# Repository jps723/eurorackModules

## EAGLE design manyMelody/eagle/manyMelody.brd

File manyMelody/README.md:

# manyMelody Synth

# **This is currently incomplete and I'll be updating shortly.** 

## To do: 
1) Write code for CV Input. 
2) Clean up synth defs
3) Adjust min/max on all parameters. 

This is a eurorack version of the [Feather Synth](https://github.com/jps723/featherSynth/), moving over to a Teensy 3.6. 

**Design Notes:**

The base software for this module uses these inputs to control an auto-advancing sequence of notes.  The knobs control the root note, the scale, the probability that the note will play, and the tempo.  Pressing the button cycles through different waveforms/oscillator types.

**Synthesizer Design**
The synth is a dual-oscillator synthesizer, each with independent bi-quad filters and envelopes.  The envelope settings are static while the filters are set to Low Pass Filters with the frequency cutoff randomly changing between two static values based on probability (math within the software -- this is unrelated to the probability knob).   

**Controls**
Root Note (Tonic)
The note from which the scale begins.  By default the notes to choose from range from A0 to C8

**Scale Selector**
There are a total of seven scales to choose from, beginning with the major scale, and then each mode variant resulting in the 7 diatonic modes in western music.

**Probability**
The probability that the note will be played, as calculated by comparing the knob’s position to a randomly generated number. Ex. 0-100% chance of playing

**Tempo**
The overall tempo of the sequence as determined by delay between each note

**Waveform Selector**
This is a series of oscillator combinations that get cycled through using the button.

## **Code**
The code is broken up into two separate files:  

**featherSynth.ino**
This is our primary code and is broken up into two sections: setup and loop.  Setup runs once, while loop cycles through continuously after the setup code has been executed. All of the code above the setup() function is required to call the library we are using (Audio.h), call our reference file (scales.h), and initialize our global variables. All of the code below the main loop() are functions that are called from either within setup() or loop().

Setup() contains code for setting audio memory allocation, pin assignment, and a function called oscillatorSetup() that is used for setting initial values of our oscillators/envelopes, etc.  These will mostly get overwritten by the loop however we want to define our instrument before the program begins to cycle.  

loop() contains the bulk of our code. We have a function called buttonHandler() that is used for managing what we want to happen when we press the button. If you find this function below, you can add further oscillator combinations.  Our potentiometer readings are assigned to the Feather pins here as well. If you want to change the order of the knobs, do it here.

The nested for() loop is used to populate the rootScaled array.  This determines what notes are in the sequence and the order that they’re arranged in.  There are two arrangements to choose from, either climbing the scale, or random selection.  Only one can be used at a time.

The frequency is calculated using a formula that stems from midi note values which are a standard form of notation for relating to frequency.

The frequency cutoff is currently assigned a 50% chance of being 7000 hz, or 2000 hz. Experiment with these numbers.

The probabilityOfPlaying variable is compared to a random value between 0 and 100.  Since probabilityOfPlaying is also a value between 0 and 100, this is treated as a percentage.  You can experiment with these values.

playOsc1() and playOsc2() functions take one argument (frequency) which is calculated via the explanation above.  These functions also contain the methods for dictating the ADSR envelope values which are hardcoded and can be adjusted and should be experimented with. The filter frequency cutoff and delayTime are also embedded in these functions, with delayTime being used to set the time between notes (our tempo).

The buttonHandler function counts the button presses and uses that count to cycle through the 7 different oscillator combinations in the switch statement.

**scales.h**
scales.h is a reference file where we have all of our different scales stored.  The base code has 7 scales (each of the diatonic modes) spread out across two octaves, with the root note at each octave playing at a 3:1 ratio to everything else.  This results in an 18 note array (an array with 18 indices), which are all a part of another array that contains each of these arrays (a total of 7).  If you were to add an 8th scale with 18 notes, then the scales[][] array should be initialized as scales[8][18].  This would also need to be changed in the .ino sketch in the rootScaled[][] array.  

Currently, if the knob is turned all the way to the left, the Ionian (major) Scale is selected.  As the knob is turned to the right, each scale from the array is played in the order that they are presented in the scales.h file.

## Build Process

**TOP**
Bit: 1/64”
Mill Time: ~3mins

**BOTTOM**
Bit: 1/32”, 1/64”
Mill Time: ~11mins

It’s easiest to solder in this order:
```
1. Vias
2. Resistor
3. Headers
4. Audio jack
5. Tactile button
6. Pots
```

Test

You will need to install the PJRC Audio Library via the IDE.  

And also the following libraries:
**CHECK THIS**

```
Adafruit_SPIFlash
Adafruit_Zero_I2S_Library
SDFat-Adafruit Fork
```

Once all of the dependencies have been installed, and you’ve uploaded a trial sketch, upload the code that you’ve downloaded from the repository.

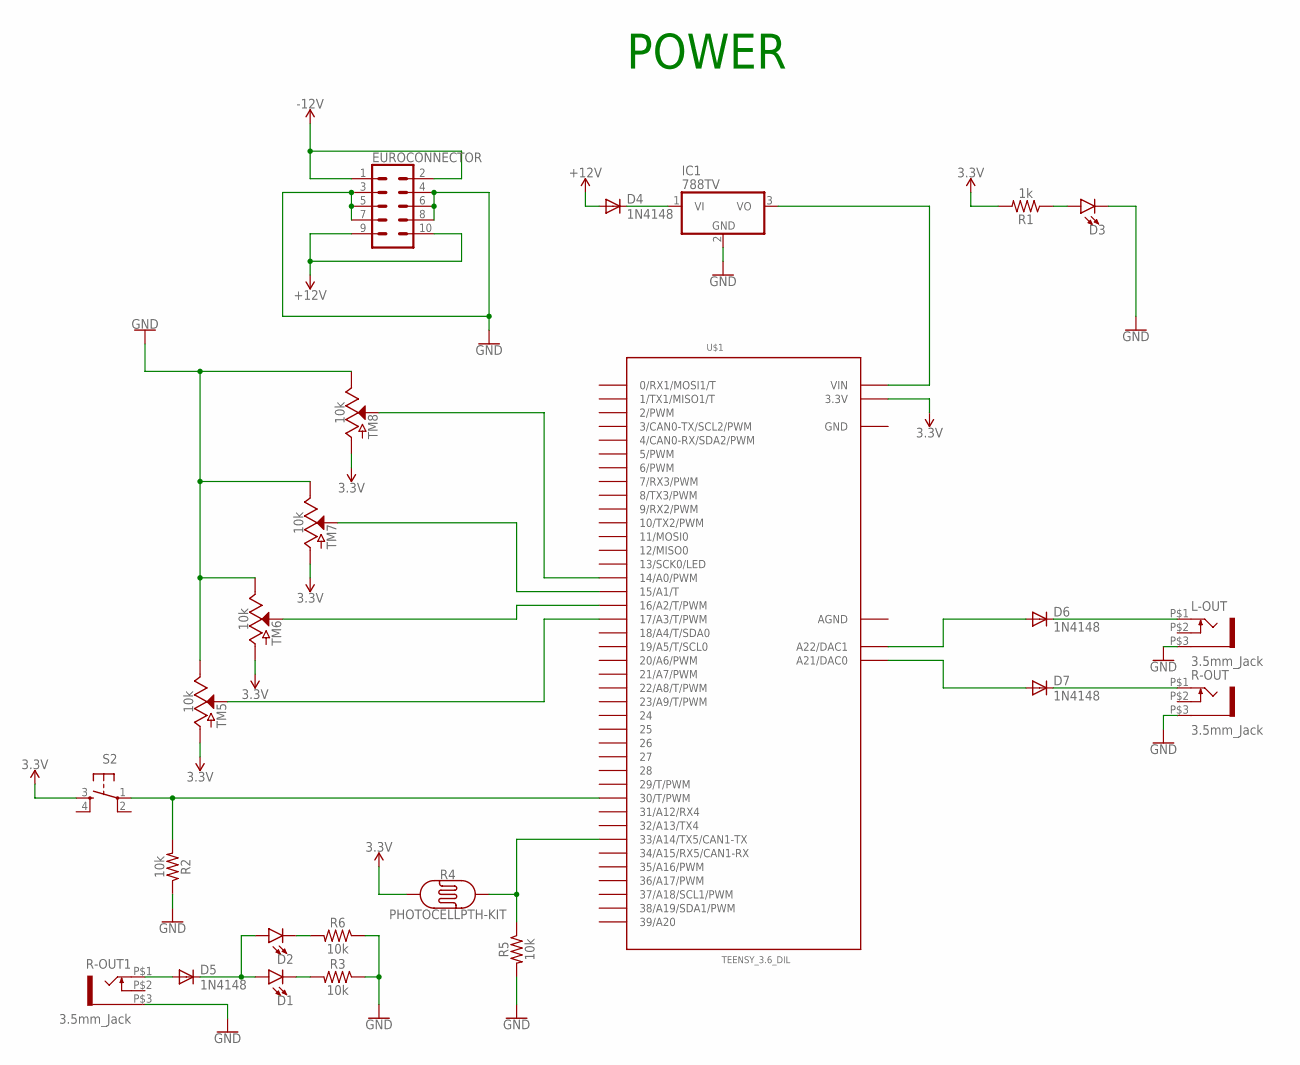
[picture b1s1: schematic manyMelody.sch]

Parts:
D1, D2, D3: LED-3MM-NO_SILK; LED_3MM-NS
D4, D5, D6, D7: 1N4148; DO41-10
EUROCONNECTOR: CONN_05X2SHD; 2X5-SHROUDED
IC1: 788TV; TO220V
L-OUT: 3.5mm_Jack; WQP-PJ301M-12_JACK
R1: 1k; AXIAL-0.3
R2, R3, R5, R6: 10k; AXIAL-0.3
R4: PHOTOCELLPTH-KIT; PHOTOCELL-KIT
R-OUT, R-OUT1: 3.5mm_Jack; WQP-PJ301M-12_JACK
S2: TAC_SWITCHPTH; TACTILE-PTH
TM5, TM6, TM7, TM8: 10k; POT-PTH-ALPS
U$1: TEENSY_3.6_DIL

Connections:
3.3V: R1.P$2 (2), R4.1, S2.3, TM5.P$3 (A), TM6.P$3 (A), TM7.P$3 (A), TM8.P$3 (A), U$1.3.3V, U$1.3.3V3 (3.3V)
5V: IC1.3 (VO), U$1.VIN
+12V: D4.A, EUROCONNECTOR.9, EUROCONNECTOR.10
-12V: EUROCONNECTOR.1, EUROCONNECTOR.2
AGND: U$1.AGND
GND: D3.K (C), EUROCONNECTOR.3, EUROCONNECTOR.4, EUROCONNECTOR.5, EUROCONNECTOR.6, EUROCONNECTOR.7, EUROCONNECTOR.8, IC1.2 (GND), L-OUT.P$3 (1), R2.P$1 (1), R3.P$1 (1), R5.P$2 (2), R6.P$1 (1), R-OUT.P$3 (1), R-OUT1.P$3 (1), TM5.P$1 (E), TM6.P$1 (E), TM7.P$1 (E), TM8.P$1 (E), U$1.GND, U$1.GND1 (GND)
unnamed: D1.A, D2.A, D5.C
unnamed: D1.K (C), R3.P$2 (2)
unnamed: R2.P$2 (2), S2.1, U$1.30 (30/T/PWM)
unnamed: R4.2, R5.P$1 (1), U$1.33/A14 (33/A14/TX5/CAN1-TX)
unnamed: D2.K (C), R6.P$2 (2)
unnamed: D3.A, R1.P$1 (1)
unnamed: D6.C, L-OUT.P$1 (2)
unnamed: D7.C, R-OUT.P$1 (2)
unnamed: D6.A, U$1.A22 (A22/DAC1)
unnamed: D7.A, U$1.A21 (A21/DAC0)
unnamed: TM8.P$2 (S), U$1.14/A0 (14/A0/PWM)
unnamed: TM7.P$2 (S), U$1.15/A1 (15/A1/T)
unnamed: TM6.P$2 (S), U$1.16/A2 (16/A2/T/PWM)
unnamed: TM5.P$2 (S), U$1.17/A3 (17/A3/T/PWM)
unnamed: D4.C, IC1.1 (VI)
unnamed: D5.A, R-OUT1.P$1 (2)

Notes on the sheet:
POWER

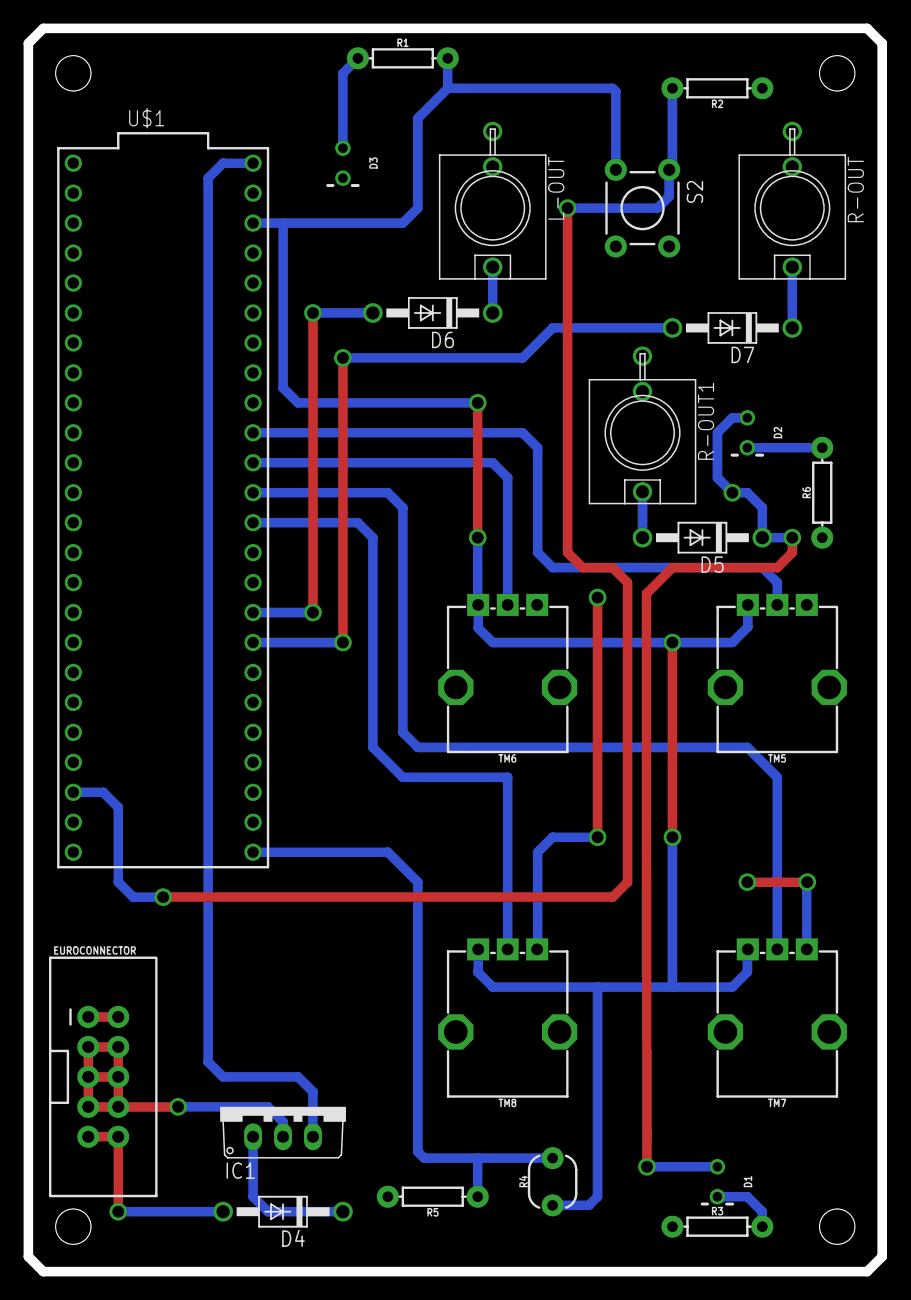
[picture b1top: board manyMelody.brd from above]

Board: 2 copper layers, 72.4 x 105.4 mm, 24 parts (0 on the bottom side), 21 nets.

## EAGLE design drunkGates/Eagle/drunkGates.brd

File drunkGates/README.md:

# Drunk Gates

This is a Eurorack format gate generator based on clock divisions and 'swing'.  It's centered around an Arduino Nano 33 iot with four gate outputs, two knob inputs, and one CV input in the form of a vactrol. The left knob controls the amount of swing, and the right knob controls the number of divisions with each output getting halved from Left-Right, Top-Bottom.  The CV input adjusts the amount of swing on each

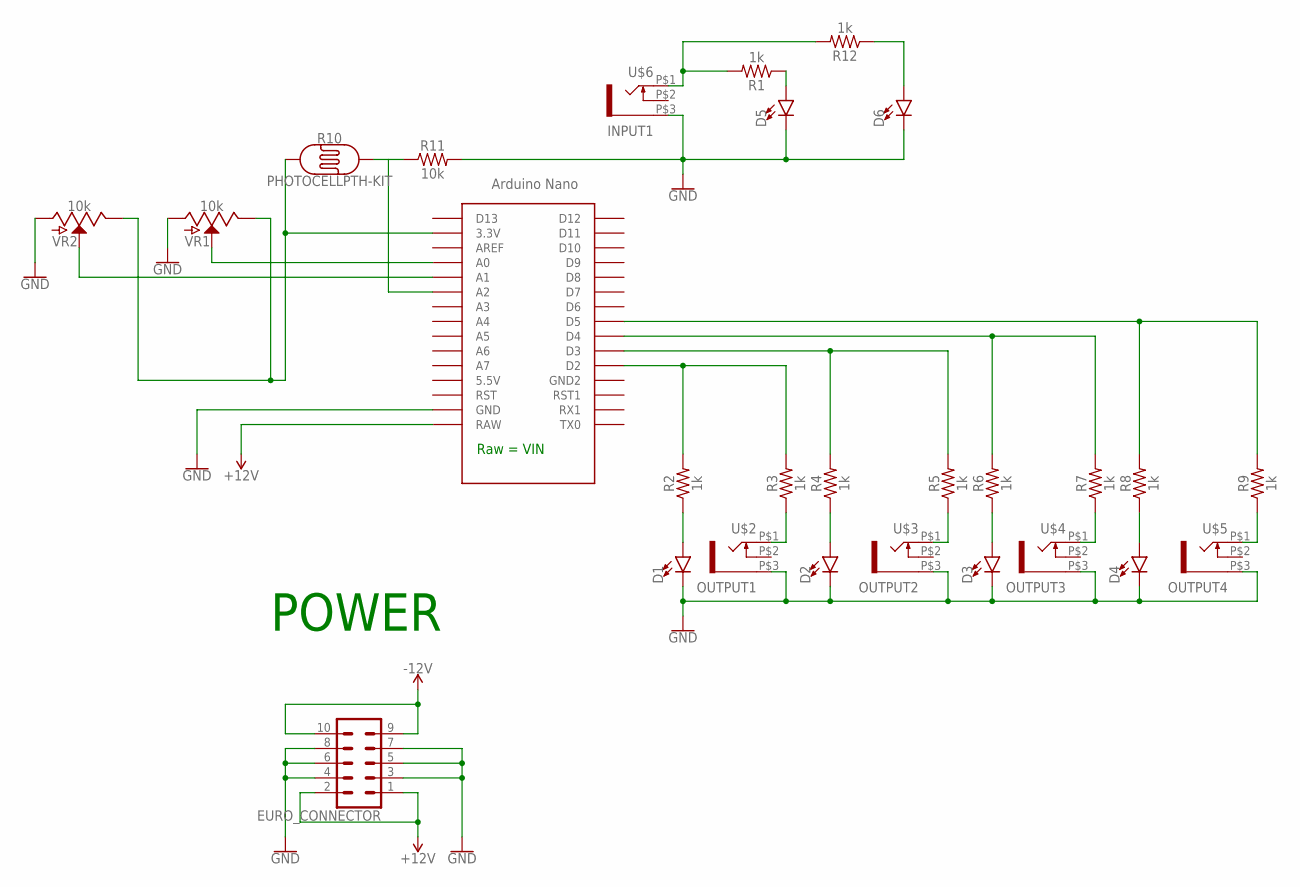
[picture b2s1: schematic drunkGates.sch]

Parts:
D1, D2, D3, D4: LED-3MM-NO_SILK; LED_3MM-NS
D5, D6: LED3MM; LED_3MM
EURO_CONNECTOR: CONN_05X2SHD; 2X5-SHROUDED
R1, R2, R3, R4, R5, R6, R7, R8, R9, R12: 1k; AXIAL-0.3
R10: PHOTOCELLPTH-KIT; PHOTOCELL-KIT
R11: 10k; AXIAL-0.3
U$1: NANO
U$2: OUTPUT1; WQP-PJ301M-12_JACK
U$3: OUTPUT2; WQP-PJ301M-12_JACK
U$4: OUTPUT3; WQP-PJ301M-12_JACK
U$5: OUTPUT4; WQP-PJ301M-12_JACK
U$6: INPUT1; WQP-PJ301M-12_JACK
VR1, VR2: 10k; POT-PTH-ALPS

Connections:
3.3V: R10.1, U$1.3.3V, VR1.P$1 (E), VR2.P$1 (E)
+12V: EURO_CONNECTOR.1, EURO_CONNECTOR.2, U$1.RAW
-12V: EURO_CONNECTOR.9, EURO_CONNECTOR.10
GND: D1.K (C), D2.K (C), D3.K (C), D4.K (C), D5.K (C), D6.K (C), EURO_CONNECTOR.3, EURO_CONNECTOR.4, EURO_CONNECTOR.5, EURO_CONNECTOR.6, EURO_CONNECTOR.7, EURO_CONNECTOR.8, R11.P$2 (2), U$1.GND, U$2.P$3 (1), U$3.P$3 (1), U$4.P$3 (1), U$5.P$3 (1), U$6.P$3 (1), VR1.P$3 (A), VR2.P$3 (A)
unnamed: U$1.A0, VR1.P$2 (S)
unnamed: U$1.A1, VR2.P$2 (S)
unnamed: D6.A, R12.P$1 (1)
unnamed: D5.A, R1.P$1 (1)
unnamed: R5.P$1 (1), U$3.P$1 (2)
unnamed: R2.P$2 (2), R3.P$2 (2), U$1.D2
unnamed: R4.P$2 (2), R5.P$2 (2), U$1.D3
unnamed: R6.P$2 (2), R7.P$2 (2), U$1.D4
unnamed: R8.P$2 (2), R9.P$2 (2), U$1.D5
unnamed: D1.A, R2.P$1 (1)
unnamed: D2.A, R4.P$1 (1)
unnamed: D3.A, R6.P$1 (1)
unnamed: D4.A, R8.P$1 (1)
unnamed: R3.P$1 (1), U$2.P$1 (2)
unnamed: R7.P$1 (1), U$4.P$1 (2)
unnamed: R10.2, R11.P$1 (1), U$1.A2
unnamed: R9.P$1 (1), U$5.P$1 (2)
unnamed: R1.P$2 (2), R12.P$2 (2), U$6.P$1 (2)

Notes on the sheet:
POWER
Raw = VIN

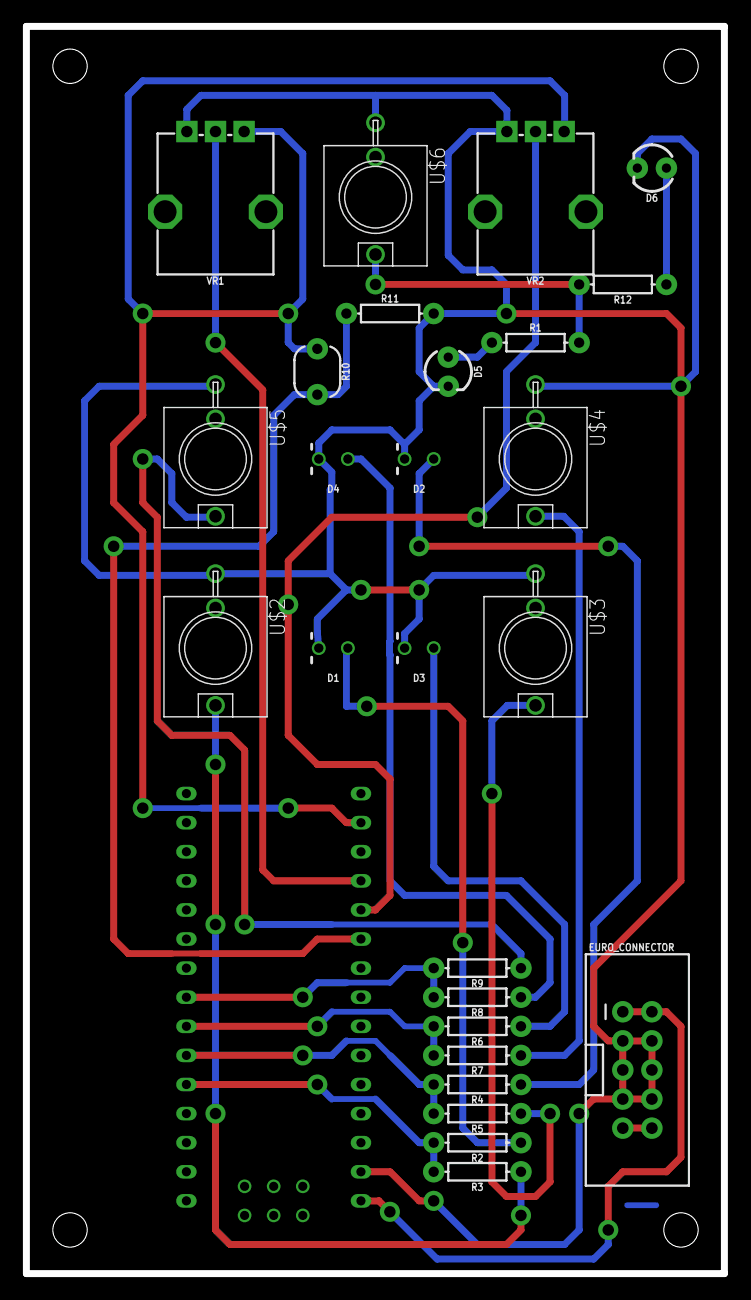
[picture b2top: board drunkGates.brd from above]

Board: 2 copper layers, 60.9 x 108.9 mm, 27 parts (1 on the bottom side), 22 nets.

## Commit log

2020-11-30 adjusted input pin definitions for teensy and for stereo output
2020-11-30 added CV Handler function
2020-12-13 minor changes to octave span and jitter levels in drunkGates

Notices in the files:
parts and their libraries:
SparkFun-Resistors: Licensing: Creative Commons ShareAlike 4.0 International - https://creativecommons.org/licenses/by-sa/4.0
